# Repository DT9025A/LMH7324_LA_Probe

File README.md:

# LMH7324_LA_Probe

使用 KiCad 进行设计的，基于 LMH7324 的 RIGOL PLA2216 逻分探头替代，在 DHO924S 上、62.5MHz 输入频率下实测可用。

# 复刻指导

1. 请依据开源工程 [MSO5000/DHO900 逻辑探头](https://oshwhub.com/zoomf1/pla2216) 中的 "转接板新版本" 打样出转接板，并购买连接器；
2. 依据本工程中的 Gerber 文件打样出探头板，请勿直接使用立创 EDA 进行导出，以免出现意外的错误（即使打 1.6mm 板厚也可以大力出奇迹焊上 1.27mm 的 IDC 连接器）；
3. 购买元器件，LMH7324 在立创商城上约 80RMB / 片；
4. 进行焊接装配。

# 主要 BOM 清单

| 值 | 封装 | 数量 | 
| :---: | :---: | :---: |
| 3.3pF | 0402 | 16 |
| 27pF | 0402 | 16 |
| 100nF | 0402 | 64 |
| 499R | 0402 | 16 |
| 300R | 0402 | 16 |
| 90.9K | 0402 | 16 |
| 10K | 0402 | 16 |
| 49R9 | 4x0603 | 8 |
| 220R | 4x0603 | 8 |
| LMH7324 | WQFN-32-1EP_5x5mm_P0.5mm_EP3.1x3.1mm | 4 |

# Test pictures

校准截图：

62.5MHz 方波输入测试：

50MHz 正弦波输入测试：

# References

- 感谢开源工程 [MSO5000/DHO900 逻辑探头](https://oshwhub.com/zoomf1/pla2216)
- 感谢 [EEVBlog](https://www.eevblog.com/forum/testgear/rpl1116-active-logic-probe-pod-for-1000z-series-teardown/) 中分享资料的各位

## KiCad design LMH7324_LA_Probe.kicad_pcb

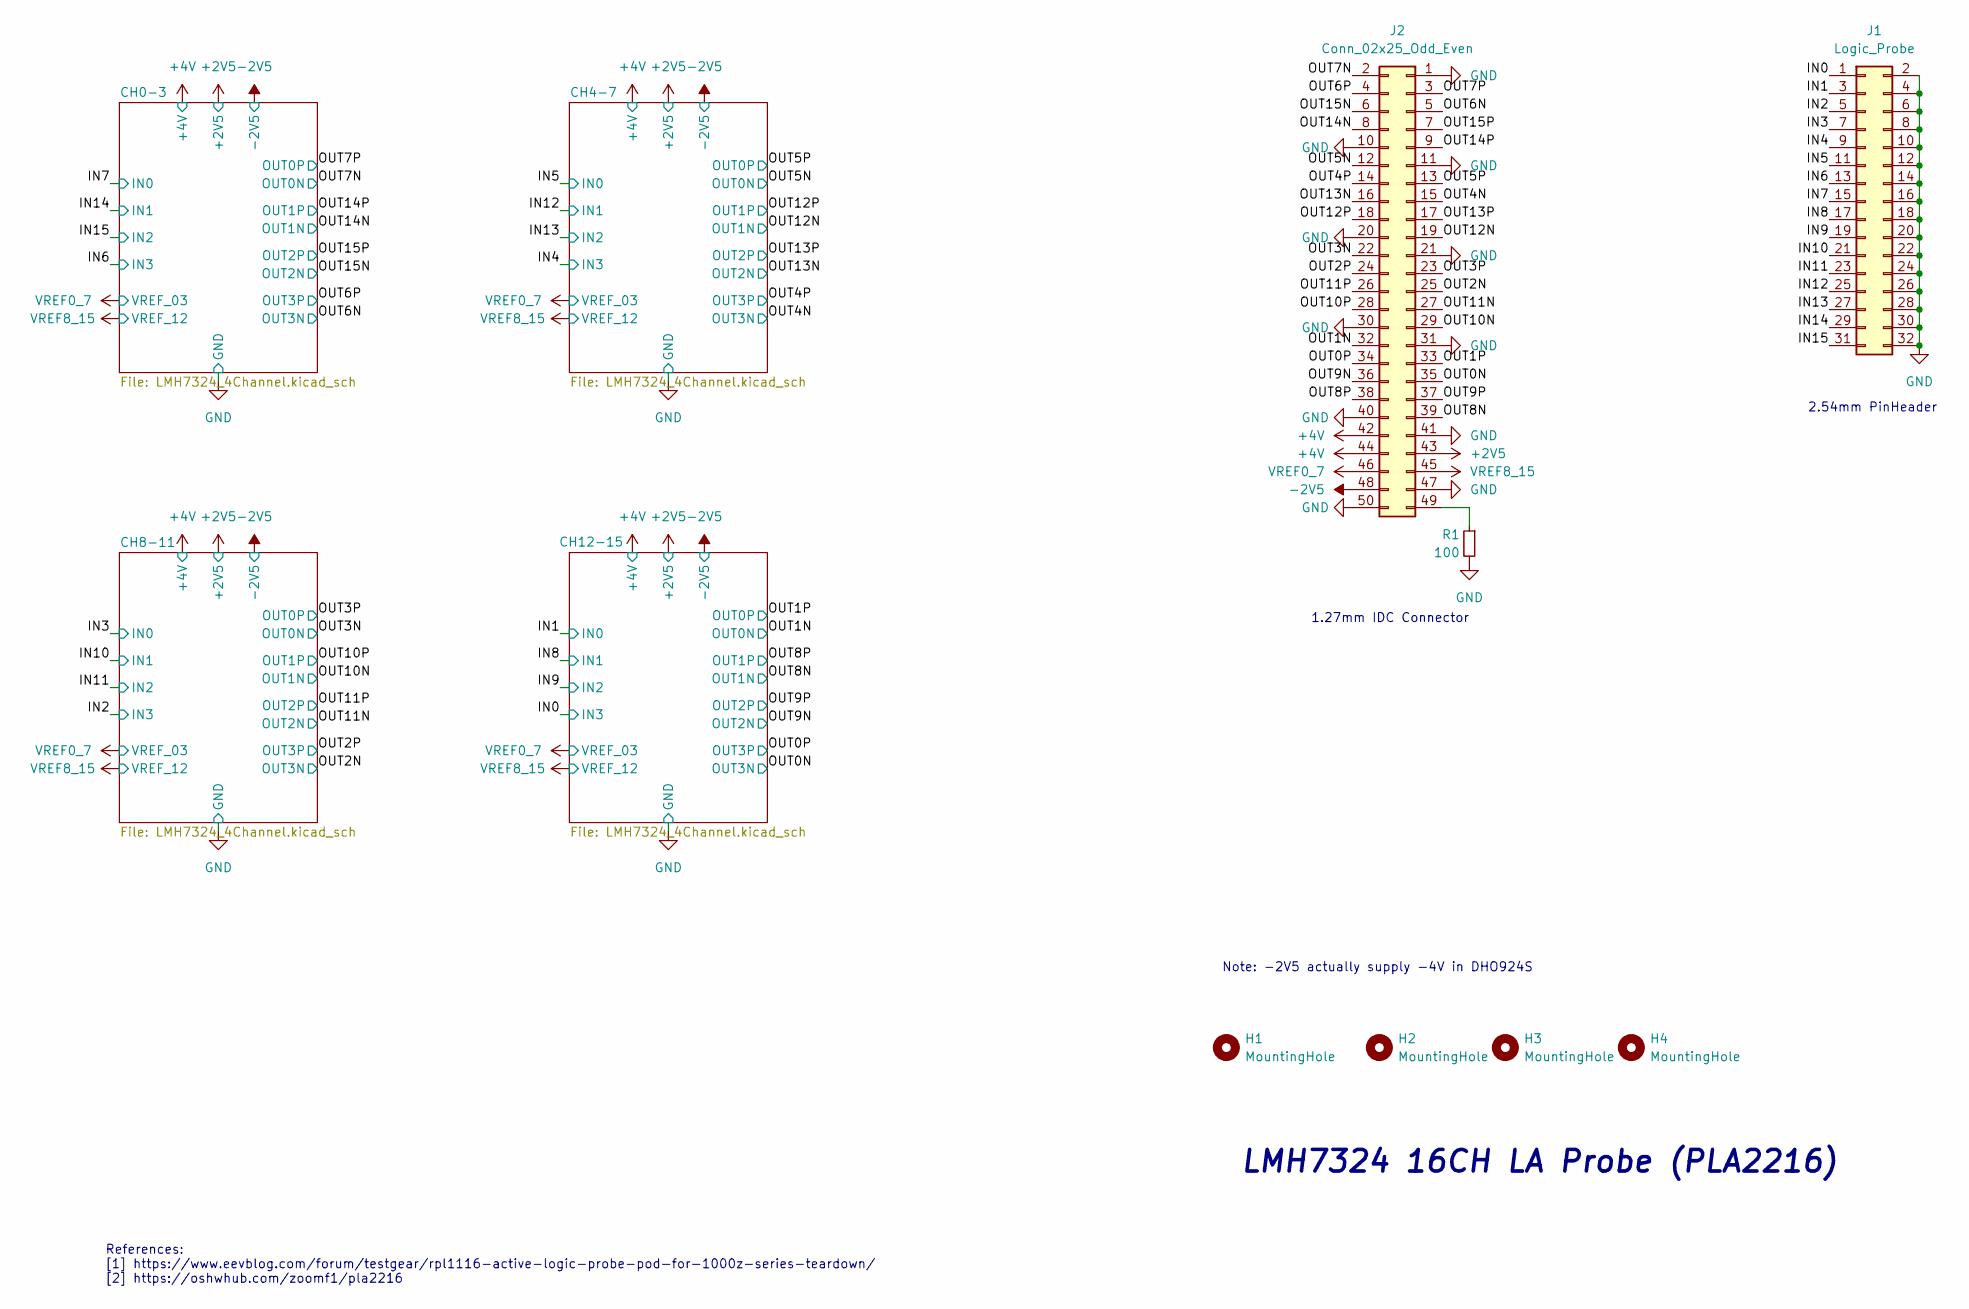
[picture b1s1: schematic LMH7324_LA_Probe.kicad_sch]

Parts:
H1, H2, H3, H4: MountingHole; MountingHole_2.2mm_M2
J1: Logic_Probe; PinHeader_02x16_2.54mm_SMD
J2: Conn_02x25_Odd_Even; PinHeader_02x25_1.27mm_SMD
R1: 100; R_0603_1608Metric; tolerance 1%; LCSC C17414

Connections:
+2V5: J2.43; also elsewhere on the board
+4V: J2.42, J2.44; also elsewhere on the board
-2V5: J2.48; also elsewhere on the board
/IN0: J1.1; also elsewhere on the board
/IN1: J1.3; also elsewhere on the board
/IN2: J1.5; also elsewhere on the board
/IN3: J1.7; also elsewhere on the board
/IN4: J1.9; also elsewhere on the board
/IN5: J1.11; also elsewhere on the board
/IN6: J1.13; also elsewhere on the board
/IN7: J1.15; also elsewhere on the board
/IN8: J1.17; also elsewhere on the board
/IN9: J1.19; also elsewhere on the board
/IN10: J1.21; also elsewhere on the board
/IN11: J1.23; also elsewhere on the board
/IN12: J1.25; also elsewhere on the board
/IN13: J1.27; also elsewhere on the board
/IN14: J1.29; also elsewhere on the board
/IN15: J1.31; also elsewhere on the board
/OUT0N: J2.35; also elsewhere on the board
/OUT0P: J2.34; also elsewhere on the board
/OUT1N: J2.32; also elsewhere on the board
/OUT1P: J2.33; also elsewhere on the board
/OUT2N: J2.25; also elsewhere on the board
/OUT2P: J2.24; also elsewhere on the board
/OUT3N: J2.22; also elsewhere on the board
/OUT3P: J2.23; also elsewhere on the board
/OUT4N: J2.15; also elsewhere on the board
/OUT4P: J2.14; also elsewhere on the board
/OUT5N: J2.12; also elsewhere on the board
/OUT5P: J2.13; also elsewhere on the board
/OUT6N: J2.5; also elsewhere on the board
/OUT6P: J2.4; also elsewhere on the board
/OUT7N: J2.2; also elsewhere on the board
/OUT7P: J2.3; also elsewhere on the board
/OUT8N: J2.39; also elsewhere on the board
/OUT8P: J2.38; also elsewhere on the board
/OUT9N: J2.36; also elsewhere on the board
/OUT9P: J2.37; also elsewhere on the board
/OUT10N: J2.29; also elsewhere on the board
/OUT10P: J2.28; also elsewhere on the board
/OUT11N: J2.27; also elsewhere on the board
/OUT11P: J2.26; also elsewhere on the board
/OUT12N: J2.19; also elsewhere on the board
/OUT12P: J2.18; also elsewhere on the board
/OUT13N: J2.16; also elsewhere on the board
/OUT13P: J2.17; also elsewhere on the board
/OUT14N: J2.8; also elsewhere on the board
/OUT14P: J2.9; also elsewhere on the board
/OUT15N: J2.6; also elsewhere on the board
/OUT15P: J2.7; also elsewhere on the board
GND: J1.2, J1.4, J1.6, J1.8, J1.10, J1.12, J1.14, J1.16, J1.18, J1.20, J1.22, J1.24, J1.26, J1.28, J1.30, J1.32, J2.1, J2.10, J2.11, J2.20, J2.21, J2.30, J2.31, J2.40, J2.41, J2.47, J2.50, R1.2; also elsewhere on the board
unnamed: J2.49, R1.1
VREF0_7: J2.46; also elsewhere on the board
VREF8_15: J2.45; also elsewhere on the board

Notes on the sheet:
References: [1] https://www.eevblog.com/forum/testgear/rpl1116-active-logic-probe-pod-for-1000z-series-teardown/ [2] https://oshwhub.com/zoomf1/pla2216
2.54mm PinHeader
1.27mm IDC Connector
LMH7324 16CH LA Probe (PLA2216)
Note: -2V5 actually supply -4V in DHO924S

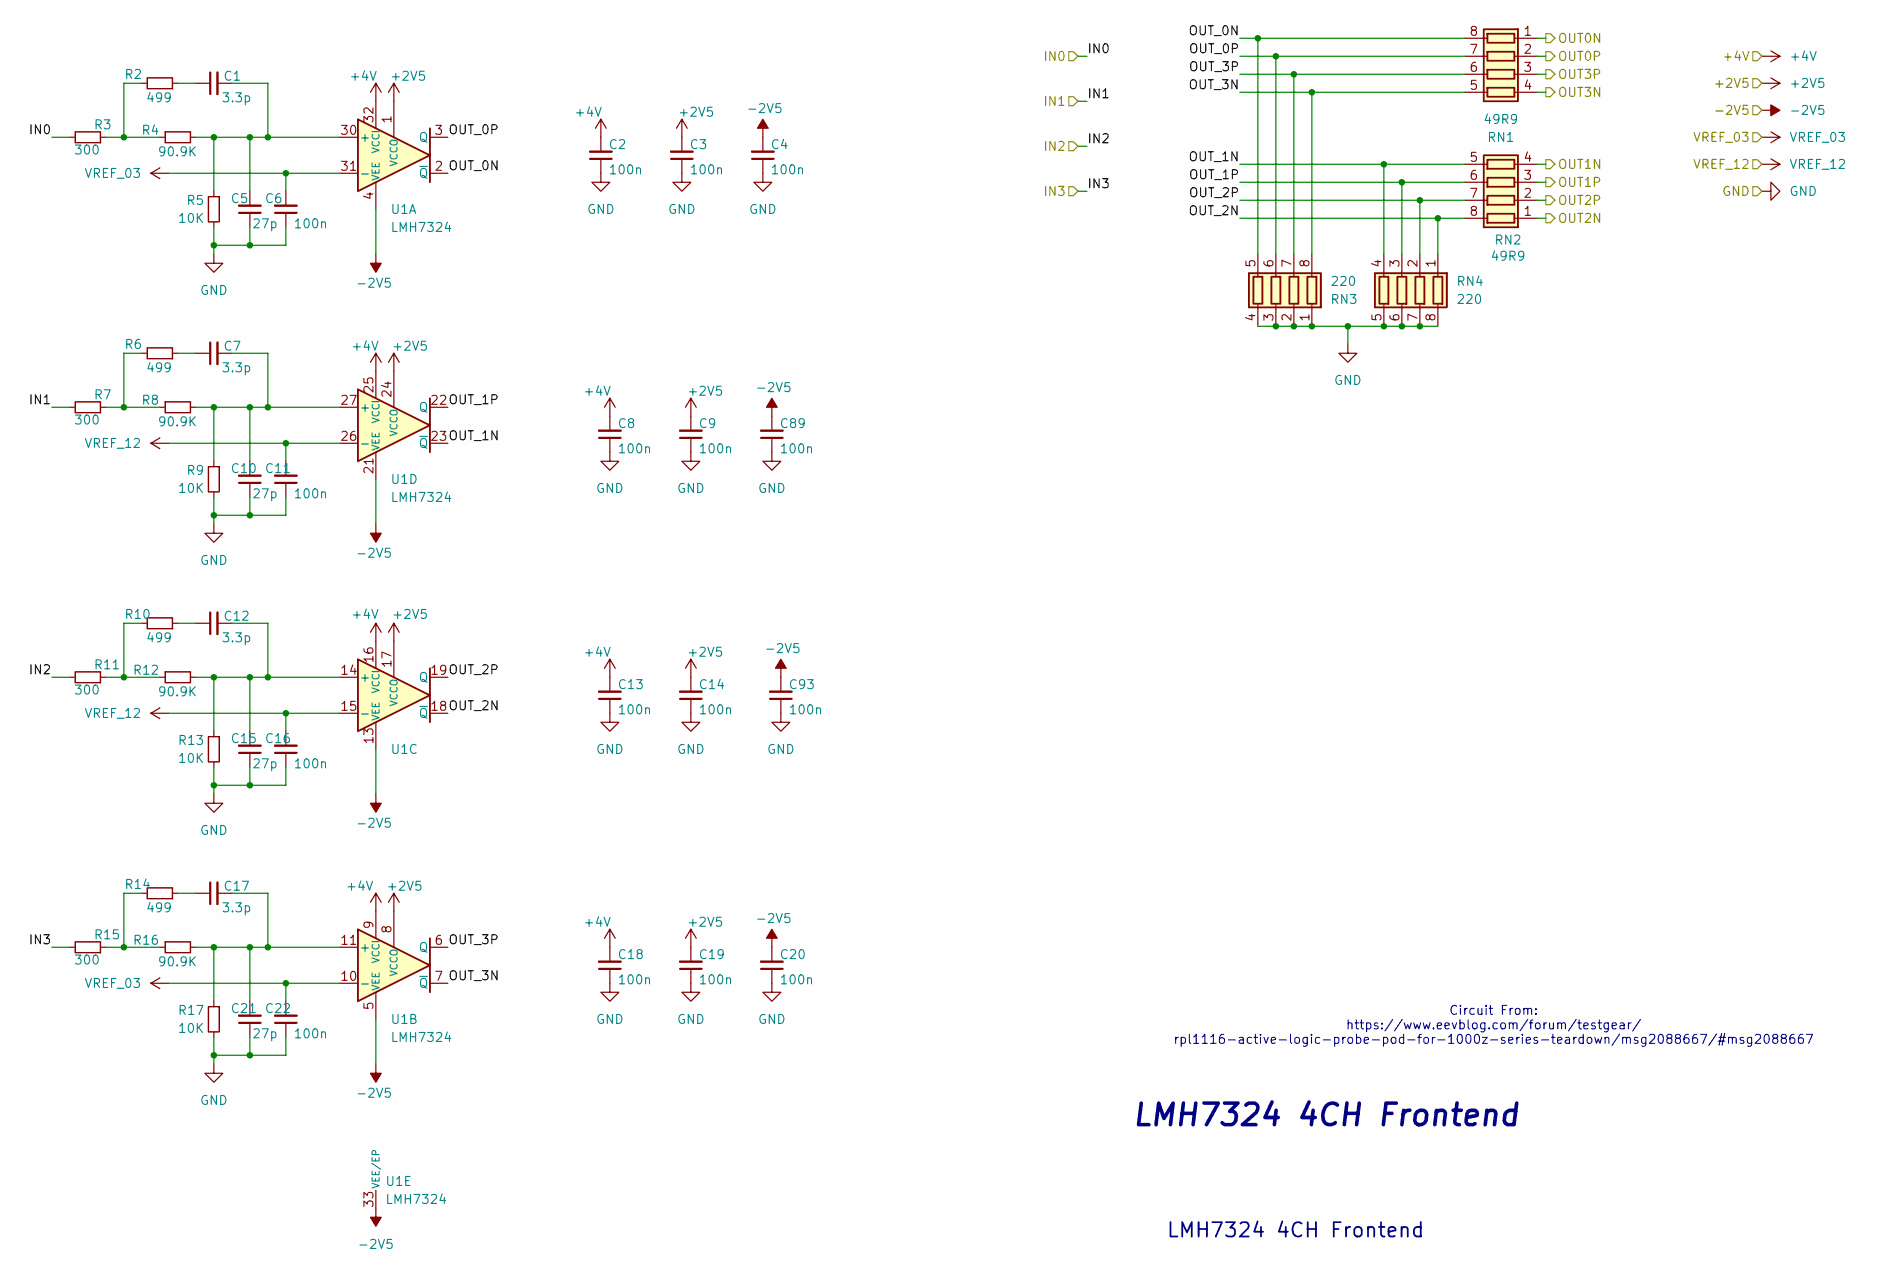
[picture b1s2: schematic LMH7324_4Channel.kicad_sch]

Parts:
C1, C7, C12, C17: 3.3p; C_0402_1005Metric; tolerance 10%; voltage 50 V; LCSC C1811
C2, C3, C4, C6, C8, C9, C11, C13, C14, C16, C18, C19, C20, C22, C89, C93: 100n; C_0402_1005Metric; tolerance 10%; voltage 50 V; LCSC C49678
C5, C10, C15, C21: 27p; C_0402_1005Metric; tolerance 10%; voltage 50 V; LCSC C1808
R2, R6, R10, R14: 499; R_0402_1005Metric; tolerance 1%; LCSC C17722
R3, R7, R11, R15: 300; R_0402_1005Metric; tolerance 1%; LCSC C17617
R4, R8, R12, R16: 90.9K; R_0402_1005Metric; tolerance 1%; LCSC C17860
R5, R9, R13, R17: 10K; R_0402_1005Metric; tolerance 1%; LCSC C17414
RN1, RN2: 49R9; R_Array_Convex_4x0603
RN3, RN4: 220; R_Array_Convex_4x0603
U1: LMH7324; WQFN-32-1EP_5x5mm_P0.5mm_EP3.1x3.1mm

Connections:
+2V5: C3.2, C9.2, C14.2, C19.2, U1.1 (VCCO), U1.8 (VCCO), U1.17 (VCCO), U1.24 (VCCO); also elsewhere on the board
+4V: C2.2, C8.2, C13.2, C18.2, U1.9 (VCCI), U1.16 (VCCI), U1.25 (VCCI), U1.32 (VCCI); also elsewhere on the board
-2V5: C4.2, C20.2, C89.2, C93.2, U1.4 (VEE), U1.5 (VEE), U1.12 (VEE), U1.13 (VEE), U1.20 (VEE), U1.21 (VEE), U1.28 (VEE), U1.29 (VEE), U1.33 (VEE/EP); also elsewhere on the board
/CH0-3/OUT_0N: RN1.8 (R1.2), RN3.5 (R4.2), U1.2 (~Q)
/CH0-3/OUT_0P: RN1.7 (R2.2), RN3.6 (R3.2), U1.3 (Q)
/CH0-3/OUT_1N: RN2.5 (R4.2), RN4.4 (R4.1), U1.23 (~Q)
/CH0-3/OUT_1P: RN2.6 (R3.2), RN4.3 (R3.1), U1.22 (Q)
/CH0-3/OUT_2N: RN2.8 (R1.2), RN4.1 (R1.1), U1.18 (~Q)
/CH0-3/OUT_2P: RN2.7 (R2.2), RN4.2 (R2.1), U1.19 (Q)
/CH0-3/OUT_3N: RN1.5 (R4.2), RN3.8 (R1.2), U1.7 (~Q)
/CH0-3/OUT_3P: RN1.6 (R3.2), RN3.7 (R2.2), U1.6 (Q)
/IN6: R15.2; also elsewhere on the board
/IN7: R3.2; also elsewhere on the board
/IN14: R7.2; also elsewhere on the board
/IN15: R11.2; also elsewhere on the board
/OUT6N: RN1.4 (R4.1); also elsewhere on the board
/OUT6P: RN1.3 (R3.1); also elsewhere on the board
/OUT7N: RN1.1 (R1.1); also elsewhere on the board
/OUT7P: RN1.2 (R2.1); also elsewhere on the board
/OUT14N: RN2.4 (R4.1); also elsewhere on the board
/OUT14P: RN2.3 (R3.1); also elsewhere on the board
/OUT15N: RN2.1 (R1.1); also elsewhere on the board
/OUT15P: RN2.2 (R2.1); also elsewhere on the board
GND: C2.1, C3.1, C4.1, C5.1, C6.1, C8.1, C9.1, C10.1, C11.1, C13.1, C14.1, C15.1, C16.1, C18.1, C19.1, C20.1, C21.1, C22.1, C89.1, C93.1, R5.2, R9.2, R13.2, R17.2, RN3.1 (R1.1), RN3.2 (R2.1), RN3.3 (R3.1), RN3.4 (R4.1), RN4.5 (R4.2), RN4.6 (R3.2), RN4.7 (R2.2), RN4.8 (R1.2); also elsewhere on the board
unnamed: C1.1, R2.1
unnamed: C7.1, R6.1
unnamed: C12.1, R10.1
unnamed: C17.1, R14.1
unnamed: R2.2, R3.1, R4.1
unnamed: R6.2, R7.1, R8.1
unnamed: R10.2, R11.1, R12.1
unnamed: R14.2, R15.1, R16.1
unnamed: C1.2, C5.2, R4.2, R5.1, U1.30 (+)
unnamed: C17.2, C21.2, R16.2, R17.1, U1.11 (+)
unnamed: C12.2, C15.2, R12.2, R13.1, U1.14 (+)
unnamed: C7.2, C10.2, R8.2, R9.1, U1.27 (+)
VREF0_7: C6.2, C22.2, U1.10 (-), U1.31 (-); also elsewhere on the board
VREF8_15: C11.2, C16.2, U1.15 (-), U1.26 (-); also elsewhere on the board

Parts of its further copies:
C23, C29, C34, C39, C45, C51, C56, C61, C67, C73, C78, C83: 3.3p; C_0402_1005Metric; tolerance 10%; voltage 50 V; LCSC C1811
C24, C25, C26, C28, C30, C31, C33, C35, C36, C38, C40, C41, C42, C44, C46, C47, C48, C50, C52, C53, C55, C57, C58, C60, C62, C63, C64, C66, C68, C69, C70, C72, C74, C75, C77, C79, C80, C82, C84, C85, C86, C88, C90, C91, C92, C94, C95, C96: 100n; C_0402_1005Metric; tolerance 10%; voltage 50 V; LCSC C49678
C27, C32, C37, C43, C49, C54, C59, C65, C71, C76, C81, C87: 27p; C_0402_1005Metric; tolerance 10%; voltage 50 V; LCSC C1808
R18, R22, R26, R30, R34, R38, R42, R46, R50, R54, R58, R62: 499; R_0402_1005Metric; tolerance 1%; LCSC C17722
R19, R23, R27, R31, R35, R39, R43, R47, R51, R55, R59, R63: 300; R_0402_1005Metric; tolerance 1%; LCSC C17617
R20, R24, R28, R32, R36, R40, R44, R48, R52, R56, R60, R64: 90.9K; R_0402_1005Metric; tolerance 1%; LCSC C17860
R21, R25, R29, R33, R37, R41, R45, R49, R53, R57, R61, R65: 10K; R_0402_1005Metric; tolerance 1%; LCSC C17414
RN5, RN6, RN9, RN10, RN13, RN14: 49R9; R_Array_Convex_4x0603
RN7, RN8, RN11, RN12, RN15, RN16: 220; R_Array_Convex_4x0603
U2, U3, U4: LMH7324; WQFN-32-1EP_5x5mm_P0.5mm_EP3.1x3.1mm

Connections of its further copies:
+2V5: C25.2, C31.2, C36.2, C41.2, C47.2, C53.2, C58.2, C63.2, C69.2, C75.2, C80.2, C85.2, U2.1 (VCCO), U2.8 (VCCO), U2.17 (VCCO), U2.24 (VCCO), U3.1 (VCCO), U3.8 (VCCO), U3.17 (VCCO), U3.24 (VCCO), U4.1 (VCCO), U4.8 (VCCO), U4.17 (VCCO), U4.24 (VCCO); also elsewhere on the board
+4V: C24.2, C30.2, C35.2, C40.2, C46.2, C52.2, C57.2, C62.2, C68.2, C74.2, C79.2, C84.2, U2.9 (VCCI), U2.16 (VCCI), U2.25 (VCCI), U2.32 (VCCI), U3.9 (VCCI), U3.16 (VCCI), U3.25 (VCCI), U3.32 (VCCI), U4.9 (VCCI), U4.16 (VCCI), U4.25 (VCCI), U4.32 (VCCI); also elsewhere on the board
-2V5: C26.2, C42.2, C48.2, C64.2, C70.2, C86.2, C90.2, C91.2, C92.2, C94.2, C95.2, C96.2, U2.4 (VEE), U2.5 (VEE), U2.12 (VEE), U2.13 (VEE), U2.20 (VEE), U2.21 (VEE), U2.28 (VEE), U2.29 (VEE), U2.33 (VEE/EP), U3.4 (VEE), U3.5 (VEE), U3.12 (VEE), U3.13 (VEE), U3.20 (VEE), U3.21 (VEE), U3.28 (VEE), U3.29 (VEE), U3.33 (VEE/EP), U4.4 (VEE), U4.5 (VEE), U4.12 (VEE), U4.13 (VEE), U4.20 (VEE), U4.21 (VEE), U4.28 (VEE), U4.29 (VEE), U4.33 (VEE/EP); also elsewhere on the board
/CH4-7/OUT_0N: RN5.8 (R1.2), RN7.5 (R4.2), U2.2 (~Q)
/CH4-7/OUT_0P: RN5.7 (R2.2), RN7.6 (R3.2), U2.3 (Q)
/CH4-7/OUT_1N: RN6.5 (R4.2), RN8.4 (R4.1), U2.23 (~Q)
/CH4-7/OUT_1P: RN6.6 (R3.2), RN8.3 (R3.1), U2.22 (Q)
/CH4-7/OUT_2N: RN6.8 (R1.2), RN8.1 (R1.1), U2.18 (~Q)
/CH4-7/OUT_2P: RN6.7 (R2.2), RN8.2 (R2.1), U2.19 (Q)
/CH4-7/OUT_3N: RN5.5 (R4.2), RN7.8 (R1.2), U2.7 (~Q)
/CH4-7/OUT_3P: RN5.6 (R3.2), RN7.7 (R2.2), U2.6 (Q)
/CH8-11/OUT_0N: RN9.8 (R1.2), RN11.5 (R4.2), U3.2 (~Q)
/CH8-11/OUT_0P: RN9.7 (R2.2), RN11.6 (R3.2), U3.3 (Q)
/CH8-11/OUT_1N: RN10.5 (R4.2), RN12.4 (R4.1), U3.23 (~Q)
/CH8-11/OUT_1P: RN10.6 (R3.2), RN12.3 (R3.1), U3.22 (Q)
/CH8-11/OUT_2N: RN10.8 (R1.2), RN12.1 (R1.1), U3.18 (~Q)
/CH8-11/OUT_2P: RN10.7 (R2.2), RN12.2 (R2.1), U3.19 (Q)
/CH8-11/OUT_3N: RN9.5 (R4.2), RN11.8 (R1.2), U3.7 (~Q)
/CH8-11/OUT_3P: RN9.6 (R3.2), RN11.7 (R2.2), U3.6 (Q)
/CH12-15/OUT_0N: RN13.8 (R1.2), RN15.5 (R4.2), U4.2 (~Q)
/CH12-15/OUT_0P: RN13.7 (R2.2), RN15.6 (R3.2), U4.3 (Q)
/CH12-15/OUT_1N: RN14.5 (R4.2), RN16.4 (R4.1), U4.23 (~Q)
/CH12-15/OUT_1P: RN14.6 (R3.2), RN16.3 (R3.1), U4.22 (Q)
/CH12-15/OUT_2N: RN14.8 (R1.2), RN16.1 (R1.1), U4.18 (~Q)
/CH12-15/OUT_2P: RN14.7 (R2.2), RN16.2 (R2.1), U4.19 (Q)
/CH12-15/OUT_3N: RN13.5 (R4.2), RN15.8 (R1.2), U4.7 (~Q)
/CH12-15/OUT_3P: RN13.6 (R3.2), RN15.7 (R2.2), U4.6 (Q)
/IN0: R63.2; also elsewhere on the board
/IN1: R51.2; also elsewhere on the board
/IN2: R47.2; also elsewhere on the board
/IN3: R35.2; also elsewhere on the board
/IN4: R31.2; also elsewhere on the board
/IN5: R19.2; also elsewhere on the board
/IN8: R55.2; also elsewhere on the board
/IN9: R59.2; also elsewhere on the board
/IN10: R39.2; also elsewhere on the board
/IN11: R43.2; also elsewhere on the board
/IN12: R23.2; also elsewhere on the board
/IN13: R27.2; also elsewhere on the board
/OUT0N: RN13.4 (R4.1); also elsewhere on the board
/OUT0P: RN13.3 (R3.1); also elsewhere on the board
/OUT1N: RN13.1 (R1.1); also elsewhere on the board
/OUT1P: RN13.2 (R2.1); also elsewhere on the board
/OUT2N: RN9.4 (R4.1); also elsewhere on the board
/OUT2P: RN9.3 (R3.1); also elsewhere on the board
/OUT3N: RN9.1 (R1.1); also elsewhere on the board
/OUT3P: RN9.2 (R2.1); also elsewhere on the board
/OUT4N: RN5.4 (R4.1); also elsewhere on the board
/OUT4P: RN5.3 (R3.1); also elsewhere on the board
/OUT5N: RN5.1 (R1.1); also elsewhere on the board
/OUT5P: RN5.2 (R2.1); also elsewhere on the board
/OUT8N: RN14.4 (R4.1); also elsewhere on the board
/OUT8P: RN14.3 (R3.1); also elsewhere on the board
/OUT9N: RN14.1 (R1.1); also elsewhere on the board
/OUT9P: RN14.2 (R2.1); also elsewhere on the board
/OUT10N: RN10.4 (R4.1); also elsewhere on the board
/OUT10P: RN10.3 (R3.1); also elsewhere on the board
/OUT11N: RN10.1 (R1.1); also elsewhere on the board
/OUT11P: RN10.2 (R2.1); also elsewhere on the board
/OUT12N: RN6.4 (R4.1); also elsewhere on the board
/OUT12P: RN6.3 (R3.1); also elsewhere on the board
/OUT13N: RN6.1 (R1.1); also elsewhere on the board
/OUT13P: RN6.2 (R2.1); also elsewhere on the board
GND: C24.1, C25.1, C26.1, C27.1, C28.1, C30.1, C31.1, C32.1, C33.1, C35.1, C36.1, C37.1, C38.1, C40.1, C41.1, C42.1, C43.1, C44.1, C46.1, C47.1, C48.1, C49.1, C50.1, C52.1, C53.1, C54.1, C55.1, C57.1, C58.1, C59.1, C60.1, C62.1, C63.1, C64.1, C65.1, C66.1, C68.1, C69.1, C70.1, C71.1, C72.1, C74.1, C75.1, C76.1, C77.1, C79.1, C80.1, C81.1, C82.1, C84.1, C85.1, C86.1, C87.1, C88.1, C90.1, C91.1, C92.1, C94.1, C95.1, C96.1, R21.2, R25.2, R29.2, R33.2, R37.2, R41.2, R45.2, R49.2, R53.2, R57.2, R61.2, R65.2, RN7.1 (R1.1), RN7.2 (R2.1), RN7.3 (R3.1), RN7.4 (R4.1), RN8.5 (R4.2), RN8.6 (R3.2), RN8.7 (R2.2), RN8.8 (R1.2), RN11.1 (R1.1), RN11.2 (R2.1), RN11.3 (R3.1), RN11.4 (R4.1), RN12.5 (R4.2), RN12.6 (R3.2), RN12.7 (R2.2), RN12.8 (R1.2), RN15.1 (R1.1), RN15.2 (R2.1), RN15.3 (R3.1), RN15.4 (R4.1), RN16.5 (R4.2), RN16.6 (R3.2), RN16.7 (R2.2), RN16.8 (R1.2); also elsewhere on the board
unnamed: C23.1, R18.1
unnamed: C29.1, R22.1
unnamed: C34.1, R26.1
unnamed: C39.1, R30.1
unnamed: C45.1, R34.1
unnamed: C51.1, R38.1
unnamed: C56.1, R42.1
unnamed: C61.1, R46.1
unnamed: C67.1, R50.1
unnamed: C73.1, R54.1
unnamed: C78.1, R58.1
unnamed: C83.1, R62.1
unnamed: R18.2, R19.1, R20.1
unnamed: R22.2, R23.1, R24.1
unnamed: R26.2, R27.1, R28.1
unnamed: R30.2, R31.1, R32.1
unnamed: R34.2, R35.1, R36.1
unnamed: R38.2, R39.1, R40.1
unnamed: R42.2, R43.1, R44.1
unnamed: R46.2, R47.1, R48.1
unnamed: R50.2, R51.1, R52.1
unnamed: R54.2, R55.1, R56.1
unnamed: R58.2, R59.1, R60.1
unnamed: R62.2, R63.1, R64.1
unnamed: C23.2, C27.2, R20.2, R21.1, U2.30 (+)
unnamed: C39.2, C43.2, R32.2, R33.1, U2.11 (+)
unnamed: C34.2, C37.2, R28.2, R29.1, U2.14 (+)
unnamed: C29.2, C32.2, R24.2, R25.1, U2.27 (+)
unnamed: C45.2, C49.2, R36.2, R37.1, U3.30 (+)
unnamed: C61.2, C65.2, R48.2, R49.1, U3.11 (+)
unnamed: C56.2, C59.2, R44.2, R45.1, U3.14 (+)
unnamed: C51.2, C54.2, R40.2, R41.1, U3.27 (+)
unnamed: C67.2, C71.2, R52.2, R53.1, U4.30 (+)
unnamed: C83.2, C87.2, R64.2, R65.1, U4.11 (+)
unnamed: C78.2, C81.2, R60.2, R61.1, U4.14 (+)
unnamed: C73.2, C76.2, R56.2, R57.1, U4.27 (+)
VREF0_7: C28.2, C44.2, C50.2, C66.2, C72.2, C88.2, U2.10 (-), U2.31 (-), U3.10 (-), U3.31 (-), U4.10 (-), U4.31 (-); also elsewhere on the board
VREF8_15: C33.2, C38.2, C55.2, C60.2, C77.2, C82.2, U2.15 (-), U2.26 (-), U3.15 (-), U3.26 (-), U4.15 (-), U4.26 (-); also elsewhere on the board

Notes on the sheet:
LMH7324 4CH Frontend
Circuit From: https://www.eevblog.com/forum/testgear/ rpl1116-active-logic-probe-pod-for-1000z-series-teardown/msg2088667/#msg2088667

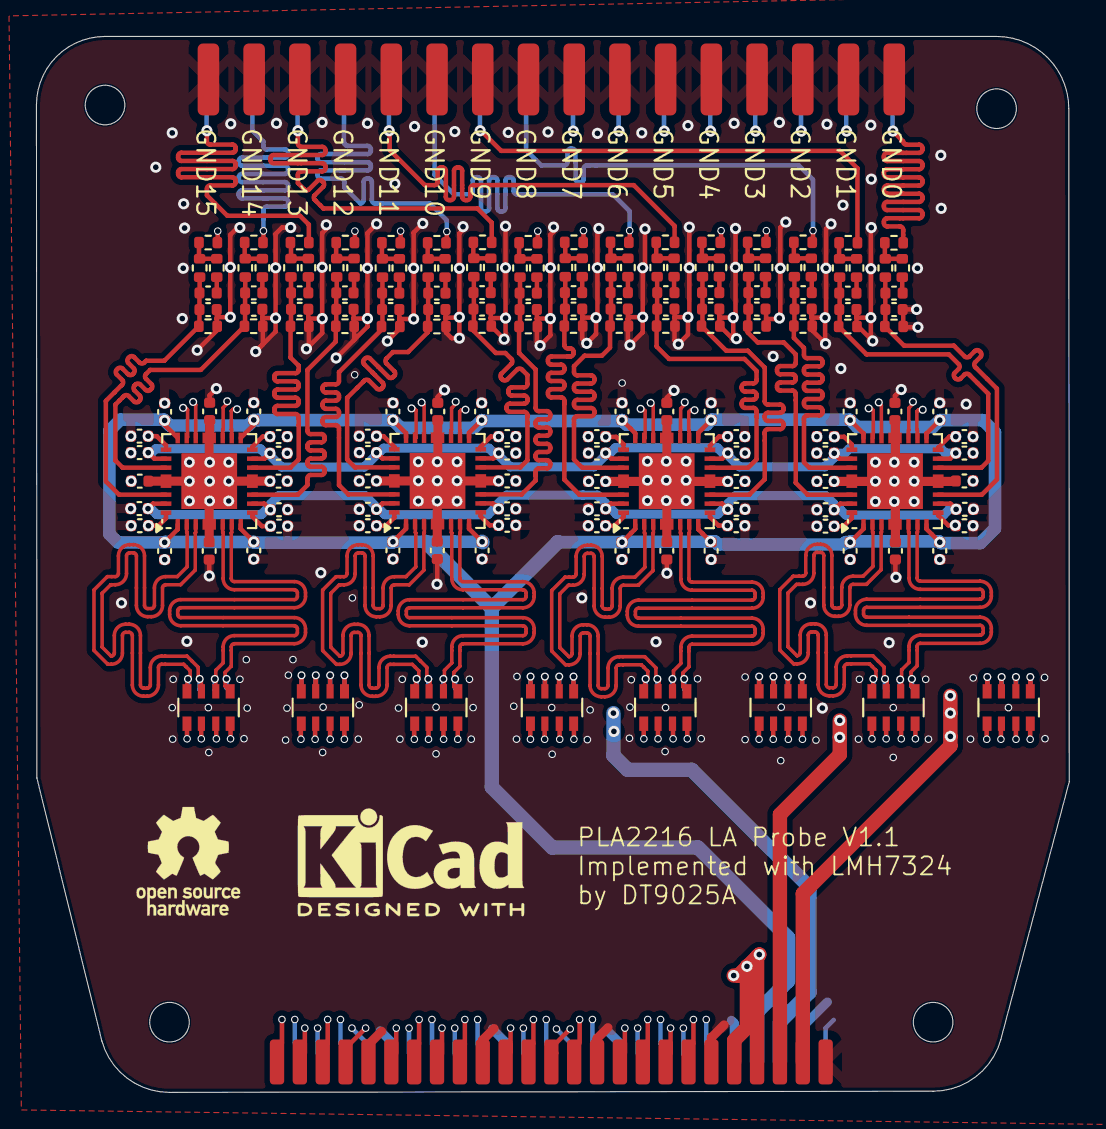
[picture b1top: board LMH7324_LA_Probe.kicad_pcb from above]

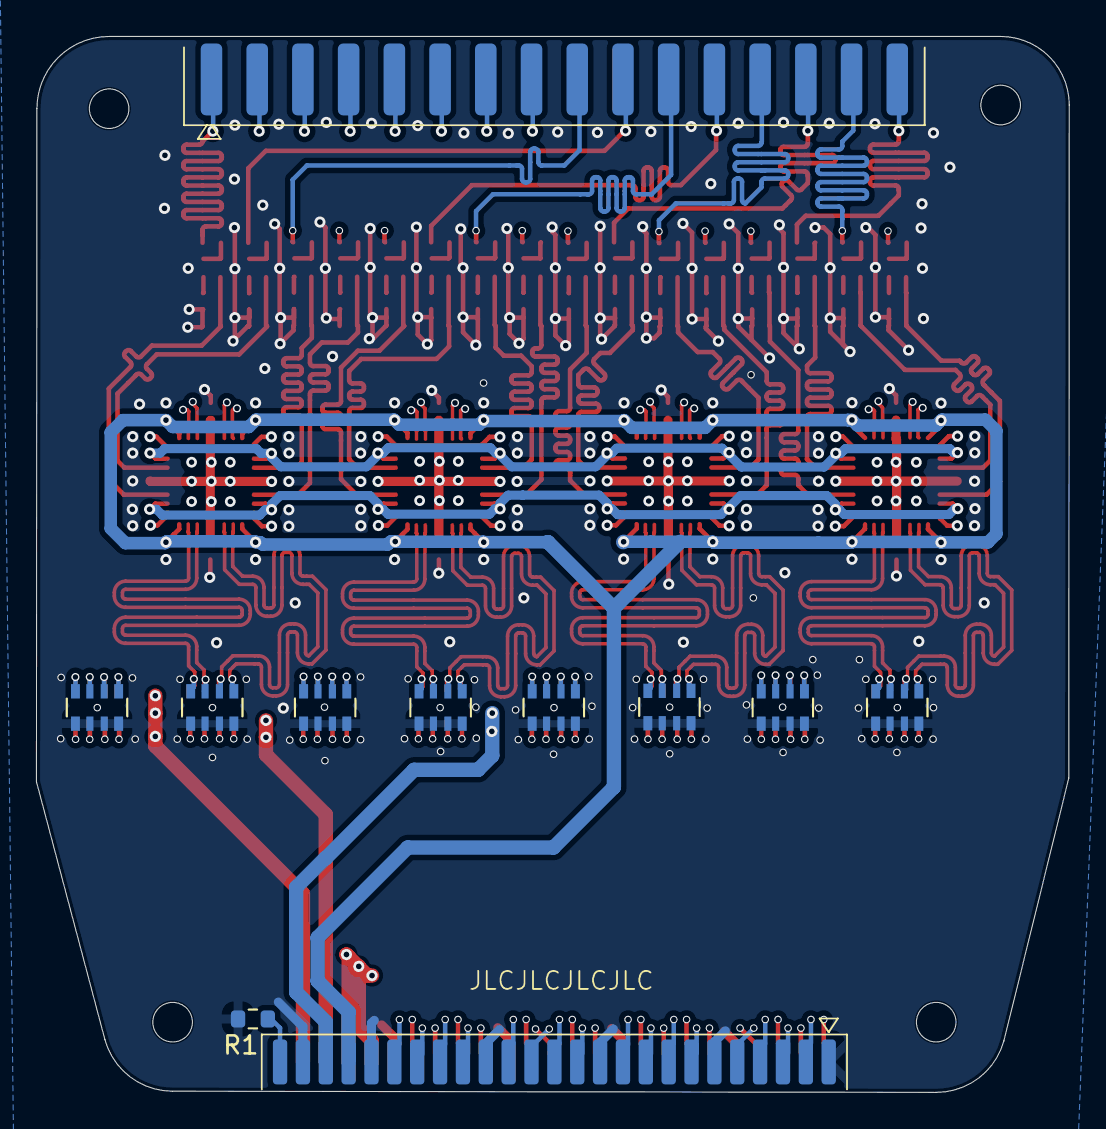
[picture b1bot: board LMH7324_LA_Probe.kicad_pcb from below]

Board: 6 copper layers, 57.4 x 58.7 mm, 187 parts (11 on the bottom side), 135 nets.

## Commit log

2025-02-09 更新了 62.5MHz 测试结果
